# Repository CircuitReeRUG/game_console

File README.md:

# game_console
name tbd

## Firmware Block Diagram

```mermaid
flowchart TD
    SD[(SD Card\nFAT32)]

    subgraph Core0 ["Core 0 -- Bootloader"]
        Menu["Menu\n- Lists .bin files from SD\n- Selects & launches game"]
        Overlay["Overlay Loop\n- Monitors A+B+UP\n- Kills game, returns to menu"]
        HAL["HAL\n- draw_pixel()\n- read_input()"]
    end

    subgraph Core1 ["Core 1 -- User Game"]
        Game["Game Binary\n- Loaded into RAM @ 0x20010000\n- Owns its own loop\n- Calls HAL only"]
    end

    subgraph Hardware ["Peripherals"]
        OLED["OLED Display\n(mutex-guarded)"]
        BTN[Buttons]
    end

    SD -->|"Read once at launch"| Menu
    Menu -->|"memcpy to 0x20010000\npush addr via FIFO"| Game
    Menu -->|"starts"| Overlay
    Overlay -->|"rp2040.restartCore1()\non A+B+UP"| Game
    Game -->|"calls"| HAL
    HAL -->|"drawPixel()"| OLED
    HAL -->|"reads"| BTN
```

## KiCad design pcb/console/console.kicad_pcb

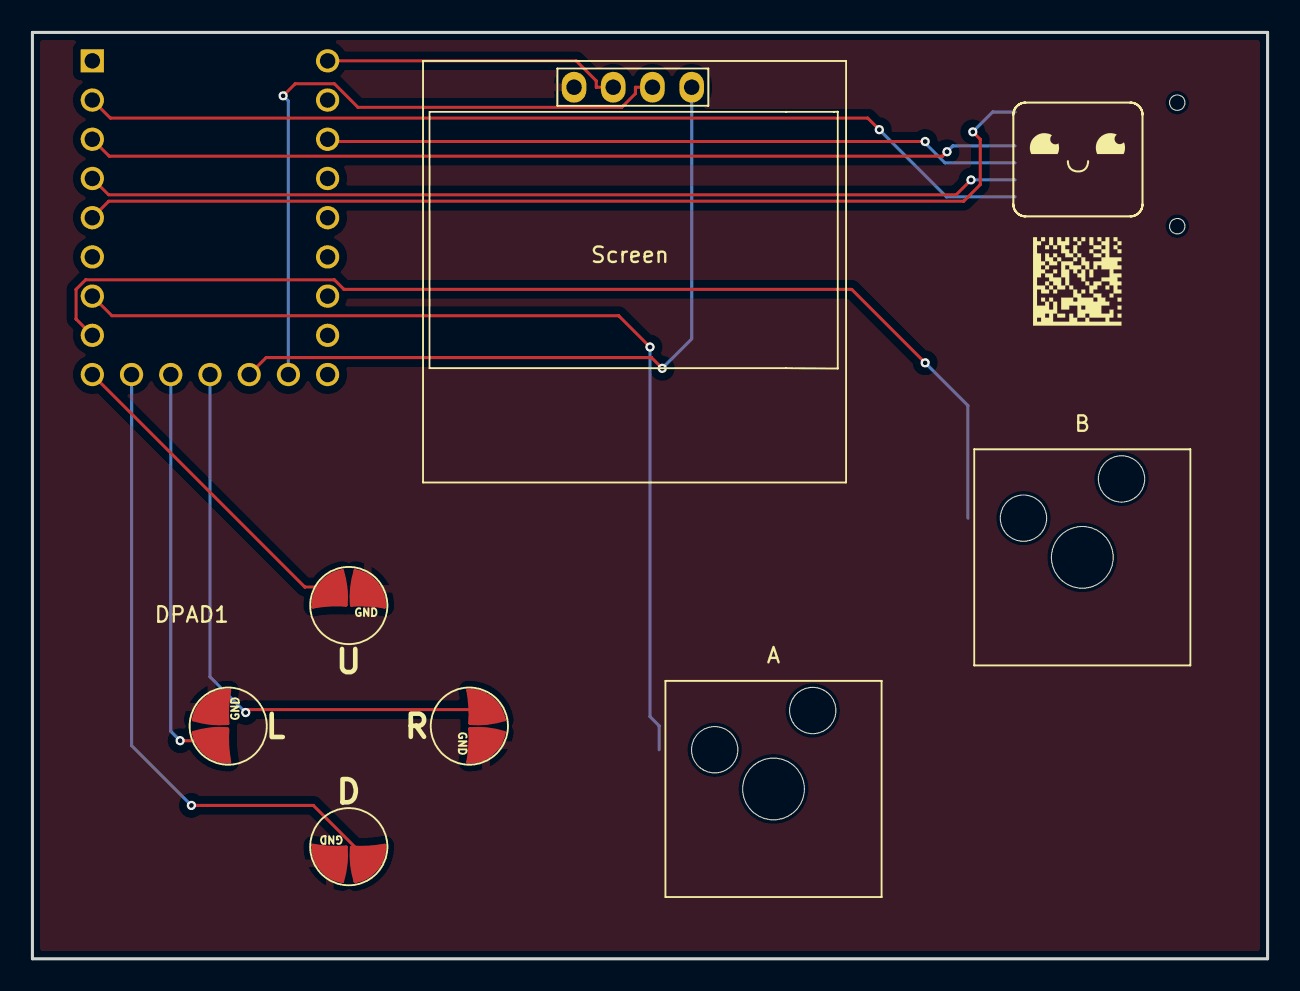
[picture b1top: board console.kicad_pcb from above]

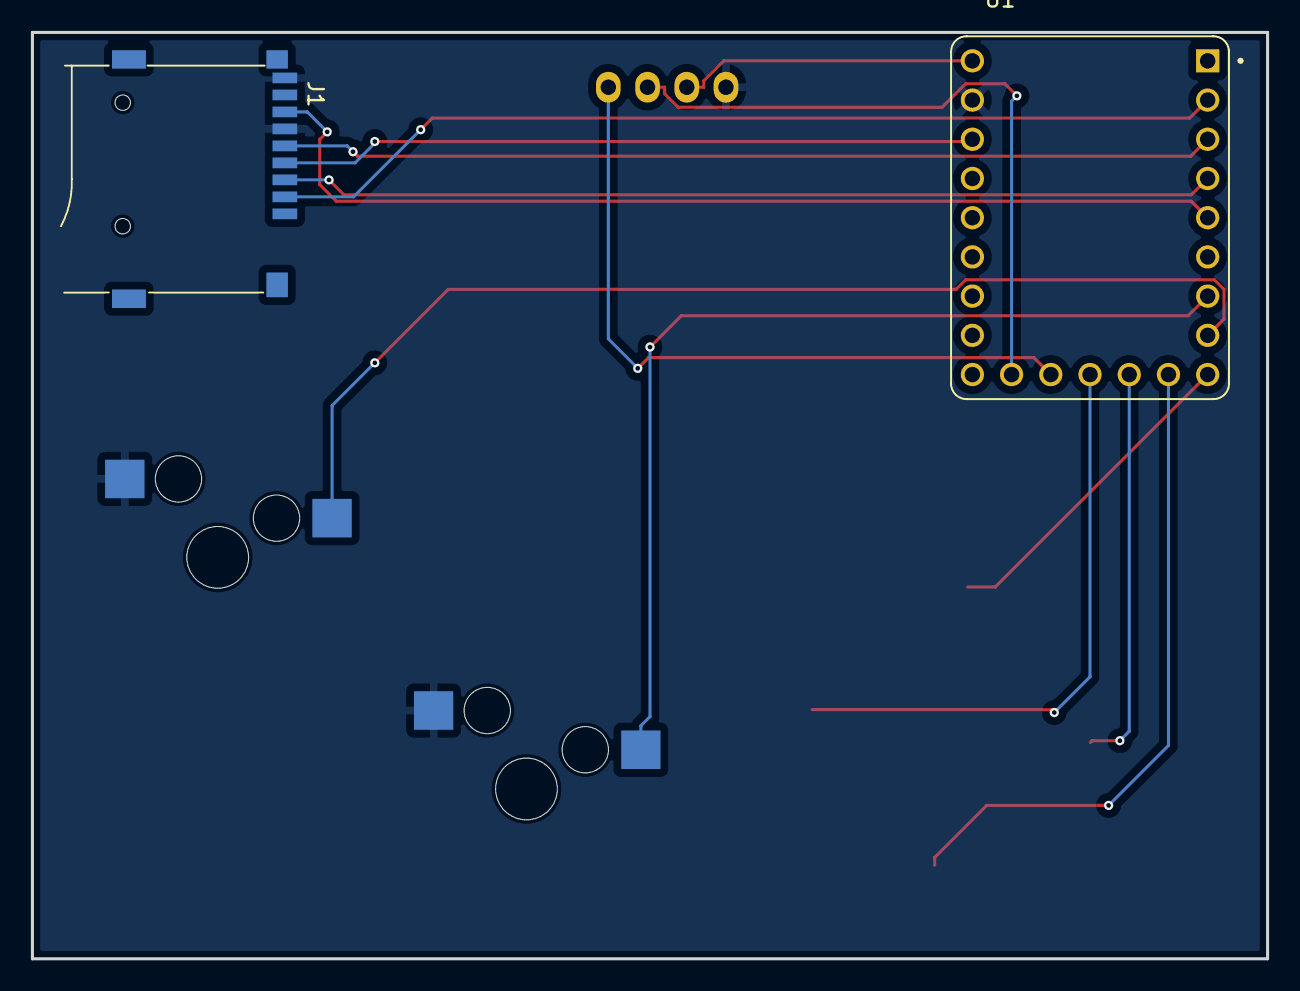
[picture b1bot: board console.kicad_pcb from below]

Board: 2 copper layers, 80.0 x 60.0 mm, 6 parts (2 on the bottom side), 15 nets.

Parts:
A: CherryMX; CherryMX_1.00u_KailhSocket
B: CherryMX; CherryMX_1.00u_KailhSocket
DPAD1: GBC; GBC DPAD
J1: SD Card; TF-015
Screen: SSD1306; 128x64OLED
U1: RP2040-ZERO; MODULE_RP2040-ZERO

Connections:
+3.3V: J1.4 (VDD), U1.21 (3V3)
+5V: Screen.2 (VCC), U1.23 (5V)
/A: A.1, U1.7 (GP6)
/B: B.1, U1.8 (GP7)
/CS: J1.2 (DAT3/CD), U1.2 (GP1)
/DOWN: DPAD1.5, U1.10 (GP9)
/LEFT: DPAD1.7, U1.11 (GP10)
/MISO: J1.7 (DAT0), U1.5 (GP4)
/MOSI: J1.3 (CMD), U1.4 (GP3)
/RIGHT: DPAD1.3, U1.12 (GP11)
/SCL0: Screen.3 (SCL), U1.14 (GP13)
/SCLK: J1.5 (CLK), U1.3 (GP2)
/SDA0: Screen.4 (SDA), U1.13 (GP12)
/UP: DPAD1.1, U1.9 (GP8)
GND: A.2, B.2, DPAD1.2, DPAD1.4, DPAD1.6, DPAD1.8, J1.6 (VSS), J1.9 (SHIELD), Screen.1 (GND), U1.22 (GND)

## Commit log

2026-02-23 strides
2026-02-28 why does this keep showing up, im not even on windows
2026-02-28 added step
2026-03-03 Code skeleton + needed libs
2026-03-12 Full testing program -- works!
2026-03-12 Final PCB design
2026-03-16 added dev
2026-03-16 Reorganization for bootloader approach
2026-03-16 update diagram
2026-03-21 "Instant" oled update
2026-03-21 #3, #2 and various fixes with new logic
2026-03-21 simpler HAL
2026-03-21 tinyusb
2026-03-25 sd write expose
2026-03-25 made a util header #6
2026-03-25 #9 clock
2026-03-27 Created interface for drawing text using a supplied font
